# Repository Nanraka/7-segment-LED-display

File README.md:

# 7 segment LED display

## What is it?
Seven-segment LEDs are commonly used to display numbers, but by combining multiple units, it is also possible to display images and arbitrary patterns.  
I built a system that controls a large number of seven-segment LEDs to display image data and custom-designed patterns as a large-scale display.

For more details, see: > https://elchika.com/article/256d17d7-ee96-4fee-8e8a-b19cc3068b17/

---
## HW

SPRESENSE was used for control.  
The seven-segment LEDs were controlled using a shift register with a dynamic (multiplexed) driving method.

The PCB design data is available here: > https://github.com/Nanraka/7-segment-LED-display/tree/main/schematics

Please refer to the table below for the connections to the display.  
To distribute the signal lines, I built a custom Arduino shield mounted on the SPRESENSE.

| Spresense Extension Board Pin | Display Pin | Description |
|-----------------------------|------------------------|------|
| D13 (SCK)                   | SCLK                   | SPI clock signal |
| D11 (MOSI)                  | SER, TSER              | Data input (branched to SER and TSER) |
| D9 (CS)                     | CS                     | Chip select (Anode-side shift register) |
| D9                          | RESET                  | Shift register output enable |
| D3                          | TRCLK                  | Chip select (Cathode-side shift register) |
| D1                          | OE                     | Shift register output enable |
| GND                         | GND                    | Ground (common reference) |

⚠️ Please connect a dedicated power supply to the VCC terminal of the seven-segment display.  
⚠️ Do not connect it to the SPRESENSE Vout 5V pin.

---
## SW

The data sent from SPRESENSE to the display is prepared in advance on a PC.  
Python is used to convert the image data to be displayed into binary data.

The software data is available here: > https://github.com/Nanraka/7-segment-LED-display/tree/main/src

### 1. `make_base_csv.py`
This script generates mask data.

### 2. `img_2_serial.py`
This script performs the following processes:

- Resizes the input image  
- Converts the image to a binary (black-and-white) format, reads it column by column, converts it into serial data, and saves the result as `.txt` and `.csv` files  
- Rearranges the serial data into an order that can be visually recognized as an image by humans, and saves it as a `.csv` file

### 3. `make_data_for_7seg.py`
This script performs the following processes:

- Loads mask data that defines the positions of the seven-segment digits  
- Combines the image serial data with the mask data to generate data for displaying on the seven-segment LEDs

### 4. `7seg_spresense.ino`
- This program sends data to the seven-segment display in LSB-first order.
- The `.txt` file generated by `make_data_for_7seg.py` is stored on a microSD card and read by the SPRESENSE for use.

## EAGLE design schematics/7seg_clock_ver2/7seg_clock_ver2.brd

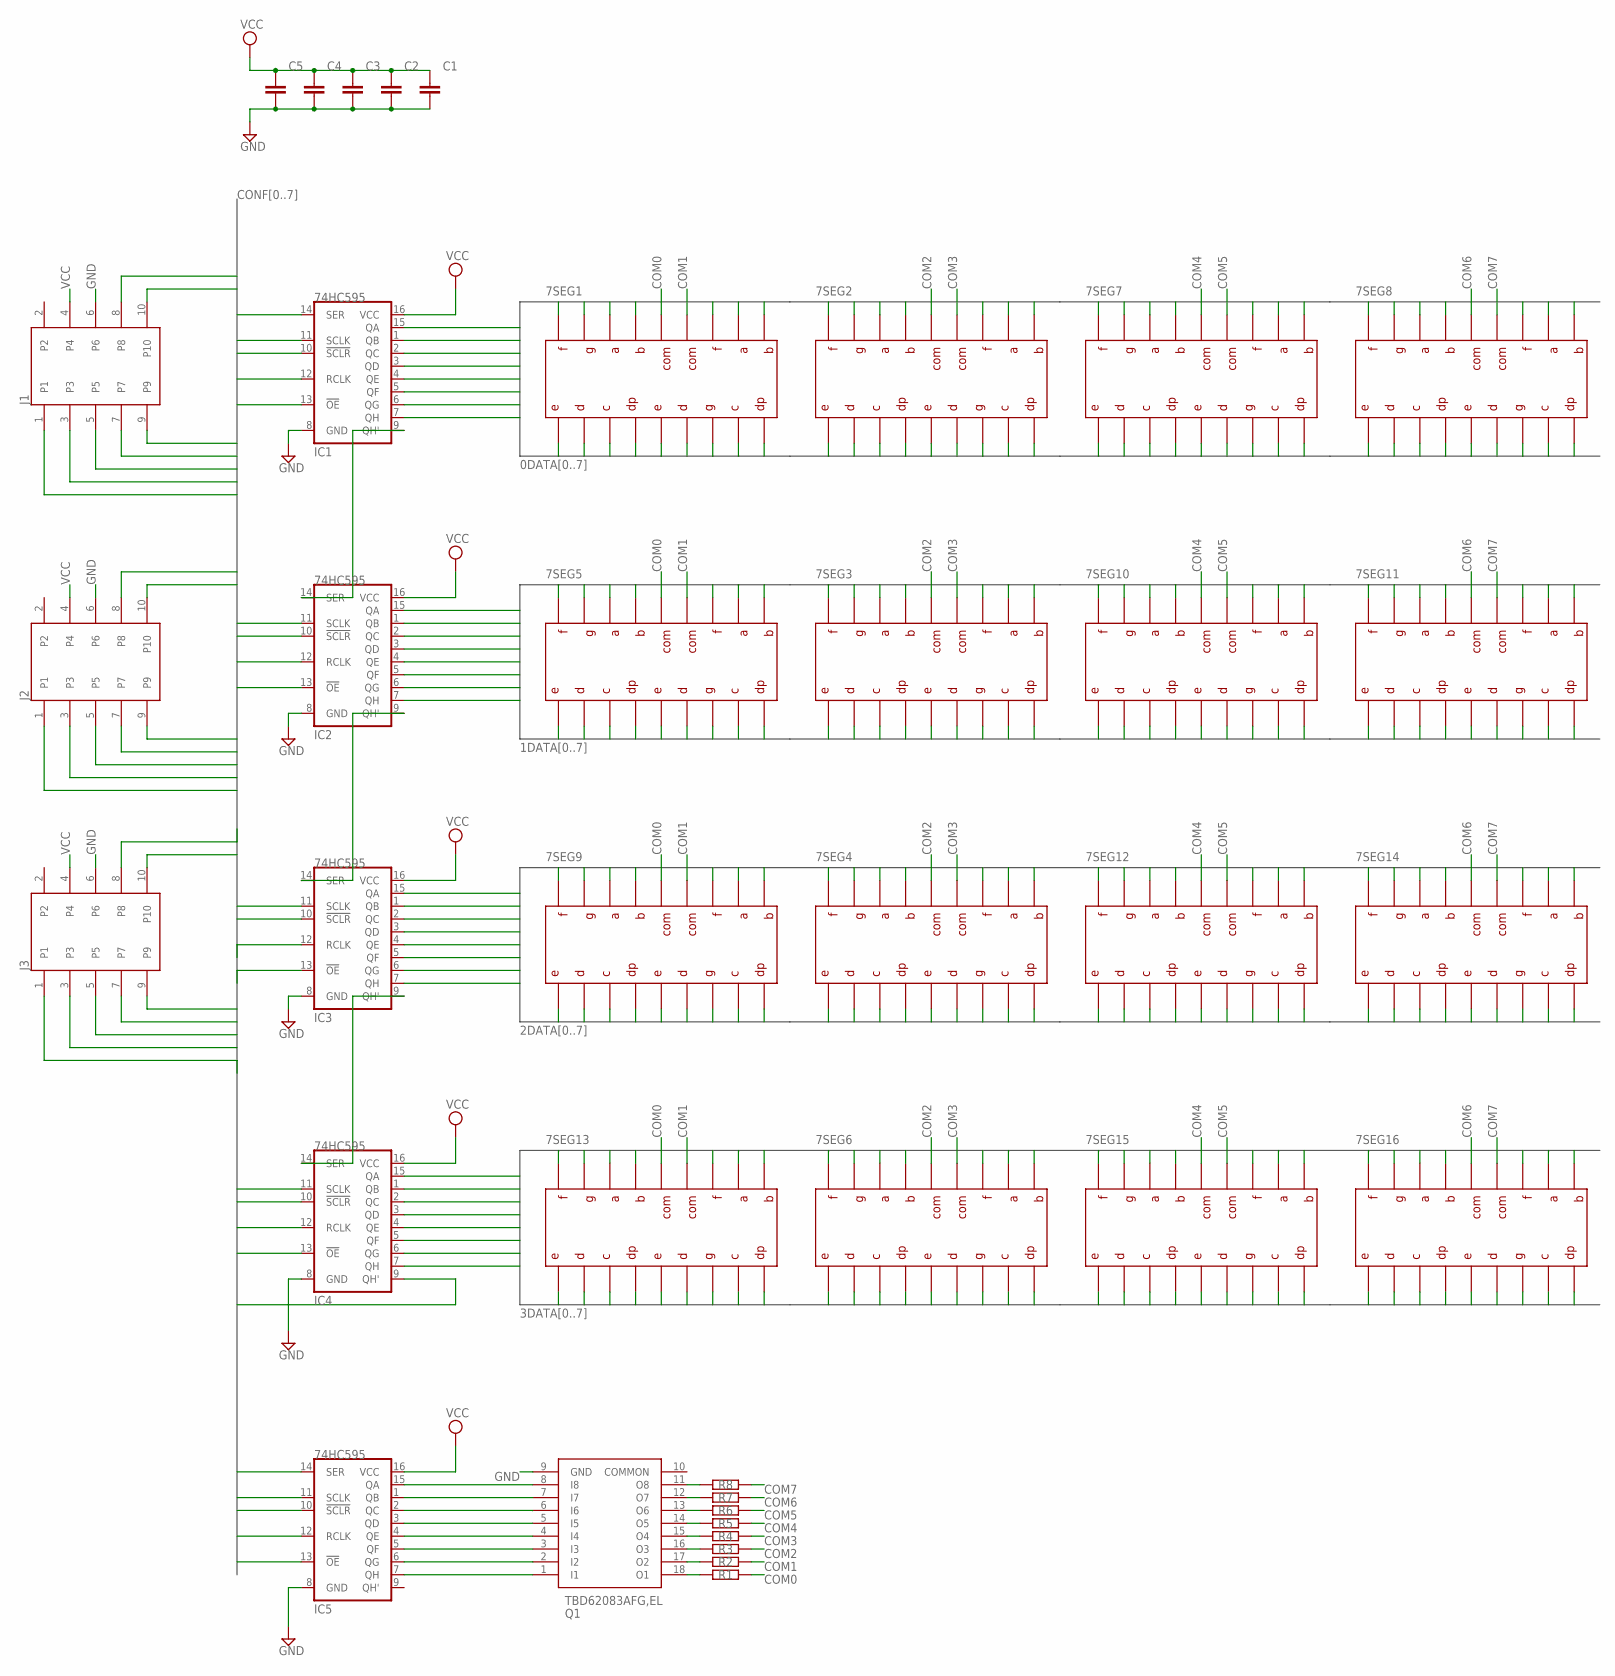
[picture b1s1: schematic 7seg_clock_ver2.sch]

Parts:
7SEG1, 7SEG2, 7SEG3, 7SEG4, 7SEG5, 7SEG6, 7SEG7, 7SEG8, 7SEG9, 7SEG10, 7SEG11, 7SEG12, 7SEG13, 7SEG14, 7SEG15, 7SEG16: SL-3264
C1, C2, C3, C4, C5: C_CHIP-0603(1608-METRIC); CAPC1608X85
IC1, IC2, IC3, IC4, IC5: 74HC595; SO16
J1, J2, J3: 1241050-5; TE_1241050-5
Q1: TBD62083AFG,EL; SOIC127P1030X245-18N
R1, R2, R3, R4, R5, R6, R7, R8: R_CHIP-0603(1608-METRIC); RESC1608X60

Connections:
0DATA0: 7SEG1.P$10, 7SEG1.P$15, 7SEG2.P$10, 7SEG2.P$15, 7SEG7.P$10, 7SEG7.P$15, 7SEG8.P$10, 7SEG8.P$15, IC1.15 (QA)
0DATA1: 7SEG1.P$12, 7SEG1.P$18, 7SEG2.P$12, 7SEG2.P$18, 7SEG7.P$12, 7SEG7.P$18, 7SEG8.P$12, 7SEG8.P$18, IC1.1 (QB)
0DATA2: 7SEG1.P$7, 7SEG1.P$17, 7SEG2.P$7, 7SEG2.P$17, 7SEG7.P$7, 7SEG7.P$17, 7SEG8.P$7, 7SEG8.P$17, IC1.2 (QC)
0DATA3: 7SEG1.P$11, 7SEG1.P$16, 7SEG2.P$11, 7SEG2.P$16, 7SEG7.P$11, 7SEG7.P$16, 7SEG8.P$11, 7SEG8.P$16, IC1.3 (QD)
0DATA4: 7SEG1.P$4, 7SEG1.P$9, 7SEG2.P$4, 7SEG2.P$9, 7SEG7.P$4, 7SEG7.P$9, 7SEG8.P$4, 7SEG8.P$9, IC1.4 (QE)
0DATA5: 7SEG1.P$3, 7SEG1.P$8, 7SEG2.P$3, 7SEG2.P$8, 7SEG7.P$3, 7SEG7.P$8, 7SEG8.P$3, 7SEG8.P$8, IC1.5 (QF)
0DATA6: 7SEG1.P$2, 7SEG1.P$6, 7SEG2.P$2, 7SEG2.P$6, 7SEG7.P$2, 7SEG7.P$6, 7SEG8.P$2, 7SEG8.P$6, IC1.6 (QG)
0DATA7: 7SEG1.P$1, 7SEG1.P$5, 7SEG2.P$1, 7SEG2.P$5, 7SEG7.P$1, 7SEG7.P$5, 7SEG8.P$1, 7SEG8.P$5, IC1.7 (QH)
1DATA0: 7SEG3.P$10, 7SEG3.P$15, 7SEG5.P$10, 7SEG5.P$15, 7SEG10.P$10, 7SEG10.P$15, 7SEG11.P$10, 7SEG11.P$15, IC2.15 (QA)
1DATA1: 7SEG3.P$12, 7SEG3.P$18, 7SEG5.P$12, 7SEG5.P$18, 7SEG10.P$12, 7SEG10.P$18, 7SEG11.P$12, 7SEG11.P$18, IC2.1 (QB)
1DATA2: 7SEG3.P$7, 7SEG3.P$17, 7SEG5.P$7, 7SEG5.P$17, 7SEG10.P$7, 7SEG10.P$17, 7SEG11.P$7, 7SEG11.P$17, IC2.2 (QC)
1DATA3: 7SEG3.P$11, 7SEG3.P$16, 7SEG5.P$11, 7SEG5.P$16, 7SEG10.P$11, 7SEG10.P$16, 7SEG11.P$11, 7SEG11.P$16, IC2.3 (QD)
1DATA4: 7SEG3.P$4, 7SEG3.P$9, 7SEG5.P$4, 7SEG5.P$9, 7SEG10.P$4, 7SEG10.P$9, 7SEG11.P$4, 7SEG11.P$9, IC2.4 (QE)
1DATA5: 7SEG3.P$3, 7SEG3.P$8, 7SEG5.P$3, 7SEG5.P$8, 7SEG10.P$3, 7SEG10.P$8, 7SEG11.P$3, 7SEG11.P$8, IC2.5 (QF)
1DATA6: 7SEG3.P$2, 7SEG3.P$6, 7SEG5.P$2, 7SEG5.P$6, 7SEG10.P$2, 7SEG10.P$6, 7SEG11.P$2, 7SEG11.P$6, IC2.6 (QG)
1DATA7: 7SEG3.P$1, 7SEG3.P$5, 7SEG5.P$1, 7SEG5.P$5, 7SEG10.P$1, 7SEG10.P$5, 7SEG11.P$1, 7SEG11.P$5, IC2.7 (QH)
2DATA0: 7SEG4.P$10, 7SEG4.P$15, 7SEG9.P$10, 7SEG9.P$15, 7SEG12.P$10, 7SEG12.P$15, 7SEG14.P$10, 7SEG14.P$15, IC3.15 (QA)
2DATA1: 7SEG4.P$12, 7SEG4.P$18, 7SEG9.P$12, 7SEG9.P$18, 7SEG12.P$12, 7SEG12.P$18, 7SEG14.P$12, 7SEG14.P$18, IC3.1 (QB)
2DATA2: 7SEG4.P$7, 7SEG4.P$17, 7SEG9.P$7, 7SEG9.P$17, 7SEG12.P$7, 7SEG12.P$17, 7SEG14.P$7, 7SEG14.P$17, IC3.2 (QC)
2DATA3: 7SEG4.P$11, 7SEG4.P$16, 7SEG9.P$11, 7SEG9.P$16, 7SEG12.P$11, 7SEG12.P$16, 7SEG14.P$11, 7SEG14.P$16, IC3.3 (QD)
2DATA4: 7SEG4.P$4, 7SEG4.P$9, 7SEG9.P$4, 7SEG9.P$9, 7SEG12.P$4, 7SEG12.P$9, 7SEG14.P$4, 7SEG14.P$9, IC3.4 (QE)
2DATA5: 7SEG4.P$3, 7SEG4.P$8, 7SEG9.P$3, 7SEG9.P$8, 7SEG12.P$3, 7SEG12.P$8, 7SEG14.P$3, 7SEG14.P$8, IC3.5 (QF)
2DATA6: 7SEG4.P$2, 7SEG4.P$6, 7SEG9.P$2, 7SEG9.P$6, 7SEG12.P$2, 7SEG12.P$6, 7SEG14.P$2, 7SEG14.P$6, IC3.6 (QG)
2DATA7: 7SEG4.P$1, 7SEG4.P$5, 7SEG9.P$1, 7SEG9.P$5, 7SEG12.P$1, 7SEG12.P$5, 7SEG14.P$1, 7SEG14.P$5, IC3.7 (QH)
3DATA0: 7SEG6.P$10, 7SEG6.P$15, 7SEG13.P$10, 7SEG13.P$15, 7SEG15.P$10, 7SEG15.P$15, 7SEG16.P$10, 7SEG16.P$15, IC4.15 (QA)
3DATA1: 7SEG6.P$12, 7SEG6.P$18, 7SEG13.P$12, 7SEG13.P$18, 7SEG15.P$12, 7SEG15.P$18, 7SEG16.P$12, 7SEG16.P$18, IC4.1 (QB)
3DATA2: 7SEG6.P$7, 7SEG6.P$17, 7SEG13.P$7, 7SEG13.P$17, 7SEG15.P$7, 7SEG15.P$17, 7SEG16.P$7, 7SEG16.P$17, IC4.2 (QC)
3DATA3: 7SEG6.P$11, 7SEG6.P$16, 7SEG13.P$11, 7SEG13.P$16, 7SEG15.P$11, 7SEG15.P$16, 7SEG16.P$11, 7SEG16.P$16, IC4.3 (QD)
3DATA4: 7SEG6.P$4, 7SEG6.P$9, 7SEG13.P$4, 7SEG13.P$9, 7SEG15.P$4, 7SEG15.P$9, 7SEG16.P$4, 7SEG16.P$9, IC4.4 (QE)
3DATA5: 7SEG6.P$3, 7SEG6.P$8, 7SEG13.P$3, 7SEG13.P$8, 7SEG15.P$3, 7SEG15.P$8, 7SEG16.P$3, 7SEG16.P$8, IC4.5 (QF)
3DATA6: 7SEG6.P$2, 7SEG6.P$6, 7SEG13.P$2, 7SEG13.P$6, 7SEG15.P$2, 7SEG15.P$6, 7SEG16.P$2, 7SEG16.P$6, IC4.6 (QG)
3DATA7: 7SEG6.P$1, 7SEG6.P$5, 7SEG13.P$1, 7SEG13.P$5, 7SEG15.P$1, 7SEG15.P$5, 7SEG16.P$1, 7SEG16.P$5, IC4.7 (QH)
COM0: 7SEG1.P$14, 7SEG5.P$14, 7SEG9.P$14, 7SEG13.P$14, R1.2
COM1: 7SEG1.P$13, 7SEG5.P$13, 7SEG9.P$13, 7SEG13.P$13, R2.2
COM2: 7SEG2.P$14, 7SEG3.P$14, 7SEG4.P$14, 7SEG6.P$14, R3.2
COM3: 7SEG2.P$13, 7SEG3.P$13, 7SEG4.P$13, 7SEG6.P$13, R4.2
COM4: 7SEG7.P$14, 7SEG10.P$14, 7SEG12.P$14, 7SEG15.P$14, R5.2
COM5: 7SEG7.P$13, 7SEG10.P$13, 7SEG12.P$13, 7SEG15.P$13, R6.2
COM6: 7SEG8.P$14, 7SEG11.P$14, 7SEG14.P$14, 7SEG16.P$14, R7.2
COM7: 7SEG8.P$13, 7SEG11.P$13, 7SEG14.P$13, 7SEG16.P$13, R8.2
CONF0: IC1.14 (SER), J1.1, J2.1, J3.1
CONF1: IC1.11 (SCLK), IC2.11 (SCLK), IC3.11 (SCLK), IC4.11 (SCLK), IC5.11 (SCLK), J1.7, J2.7, J3.7
CONF2: IC1.10 (!SCLR), IC2.10 (!SCLR), IC3.10 (!SCLR), IC4.10 (!SCLR), IC5.10 (!SCLR), J1.9, J2.9, J3.9
CONF3: IC1.12 (RCLK), IC2.12 (RCLK), IC3.12 (RCLK), IC4.12 (RCLK), IC5.12 (RCLK), J1.5, J2.5, J3.5
CONF4: IC1.13 (!OE), IC2.13 (!OE), IC3.13 (!OE), IC4.13 (!OE), IC5.13 (!OE), J1.3, J2.3, J3.3
CONF5: IC4.9 (QH'), J1.10, J2.10, J3.10
CONF6: IC5.14 (SER), J1.8, J2.8, J3.8
GND: C1.2, C2.2, C3.2, C4.2, C5.2, IC1.8 (GND), IC2.8 (GND), IC3.8 (GND), IC4.8 (GND), IC5.8 (GND), J1.6, J2.6, J3.6, Q1.9 (GND)
unnamed: IC1.9 (QH'), IC2.14 (SER)
unnamed: Q1.18 (O1), R1.1
unnamed: Q1.17 (O2), R2.1
unnamed: IC3.9 (QH'), IC4.14 (SER)
unnamed: Q1.16 (O3), R3.1
unnamed: IC5.7 (QH), Q1.1 (I1)
unnamed: IC5.6 (QG), Q1.2 (I2)
unnamed: IC5.5 (QF), Q1.3 (I3)
unnamed: IC5.4 (QE), Q1.4 (I4)
unnamed: Q1.15 (O4), R4.1
unnamed: Q1.14 (O5), R5.1
unnamed: IC5.3 (QD), Q1.5 (I5)
unnamed: IC5.2 (QC), Q1.6 (I6)
unnamed: IC5.1 (QB), Q1.7 (I7)
unnamed: IC5.15 (QA), Q1.8 (I8)
unnamed: Q1.13 (O6), R6.1
unnamed: Q1.12 (O7), R7.1
unnamed: Q1.11 (O8), R8.1
unnamed: IC2.9 (QH'), IC3.14 (SER)
VCC: C1.1, C2.1, C3.1, C4.1, C5.1, IC1.16 (VCC), IC2.16 (VCC), IC3.16 (VCC), IC4.16 (VCC), IC5.16 (VCC), J1.4, J2.4, J3.4

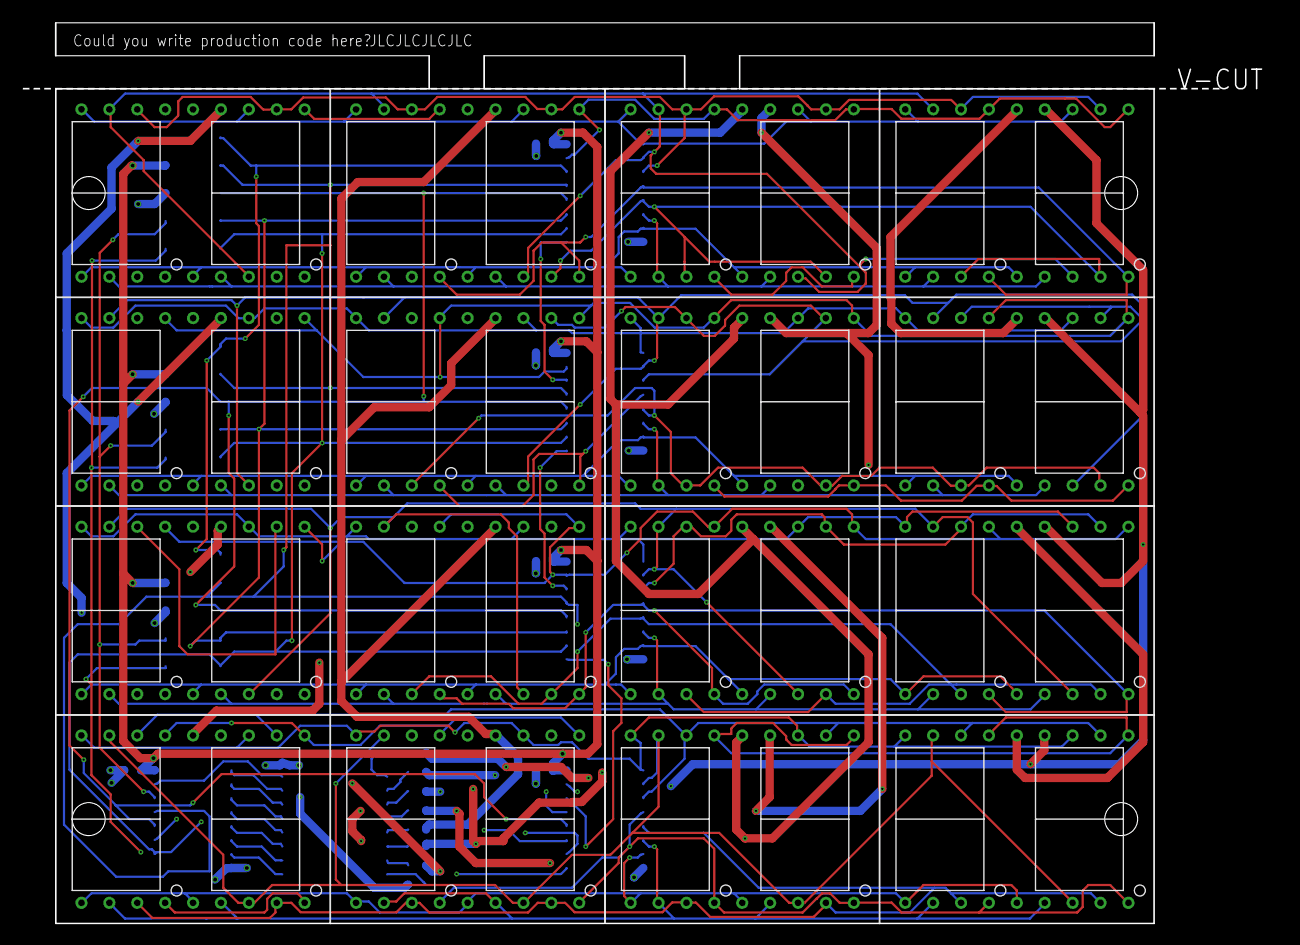
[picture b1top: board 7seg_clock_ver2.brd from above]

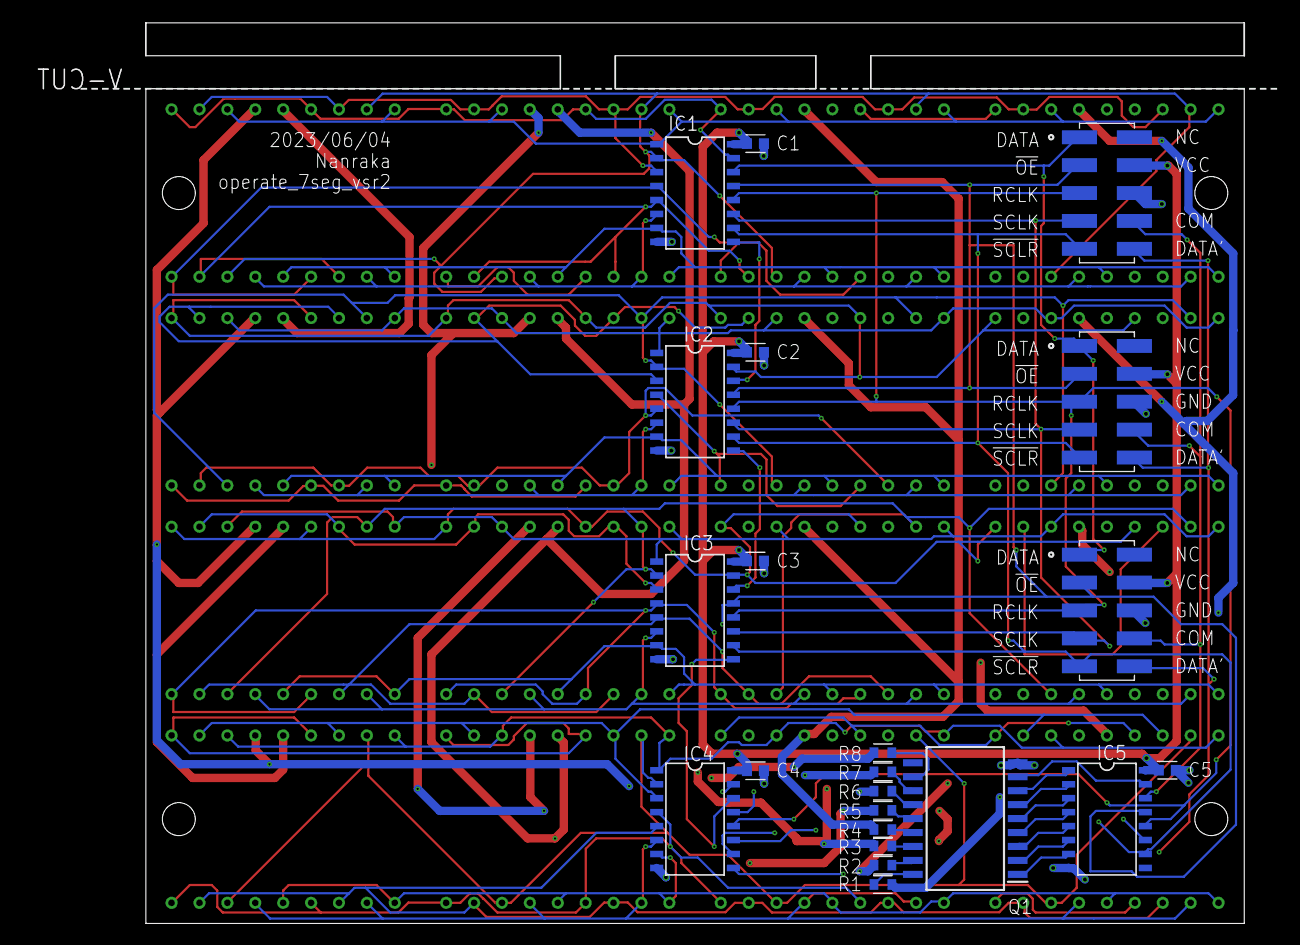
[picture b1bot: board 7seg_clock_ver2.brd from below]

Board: 4 copper layers, 114.2 x 81.9 mm, 38 parts (22 on the bottom side), 68 nets.

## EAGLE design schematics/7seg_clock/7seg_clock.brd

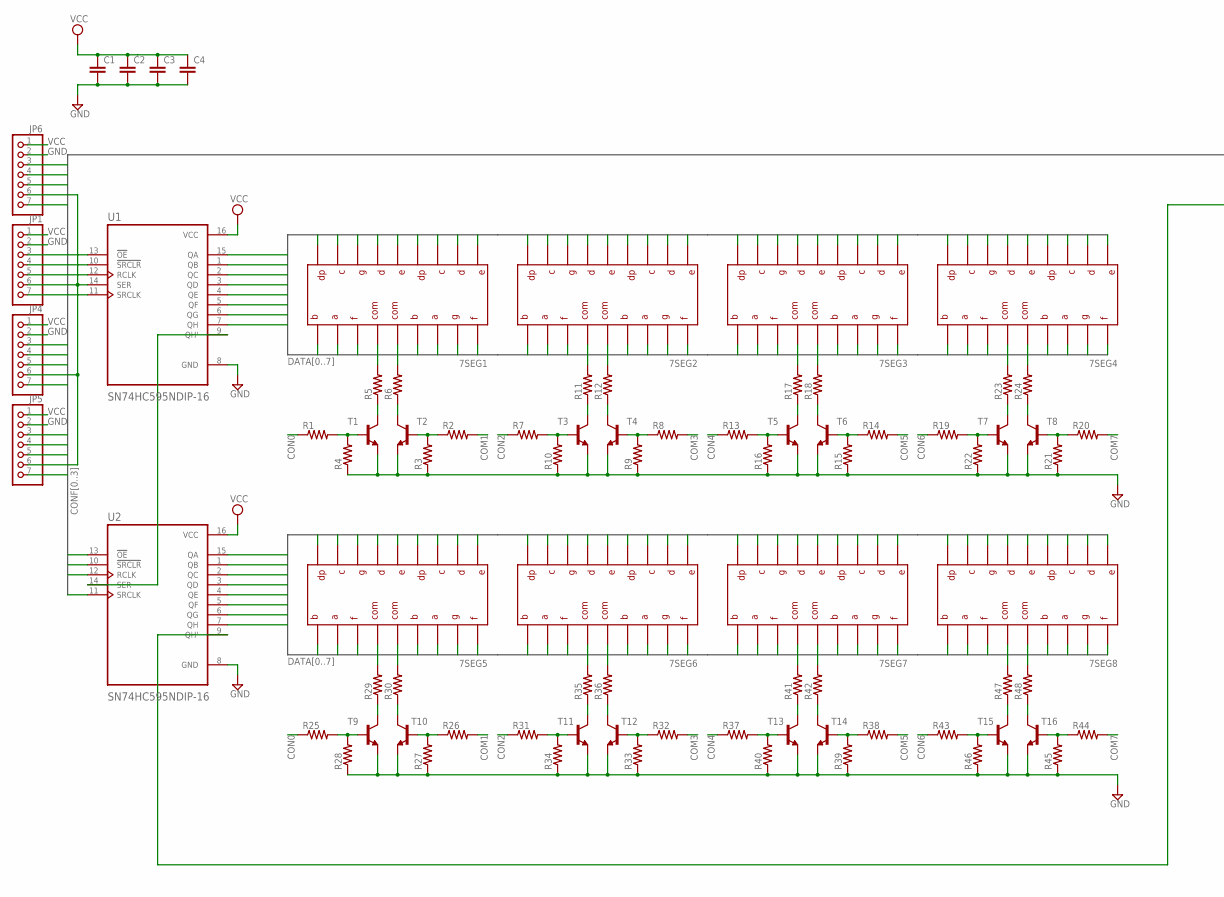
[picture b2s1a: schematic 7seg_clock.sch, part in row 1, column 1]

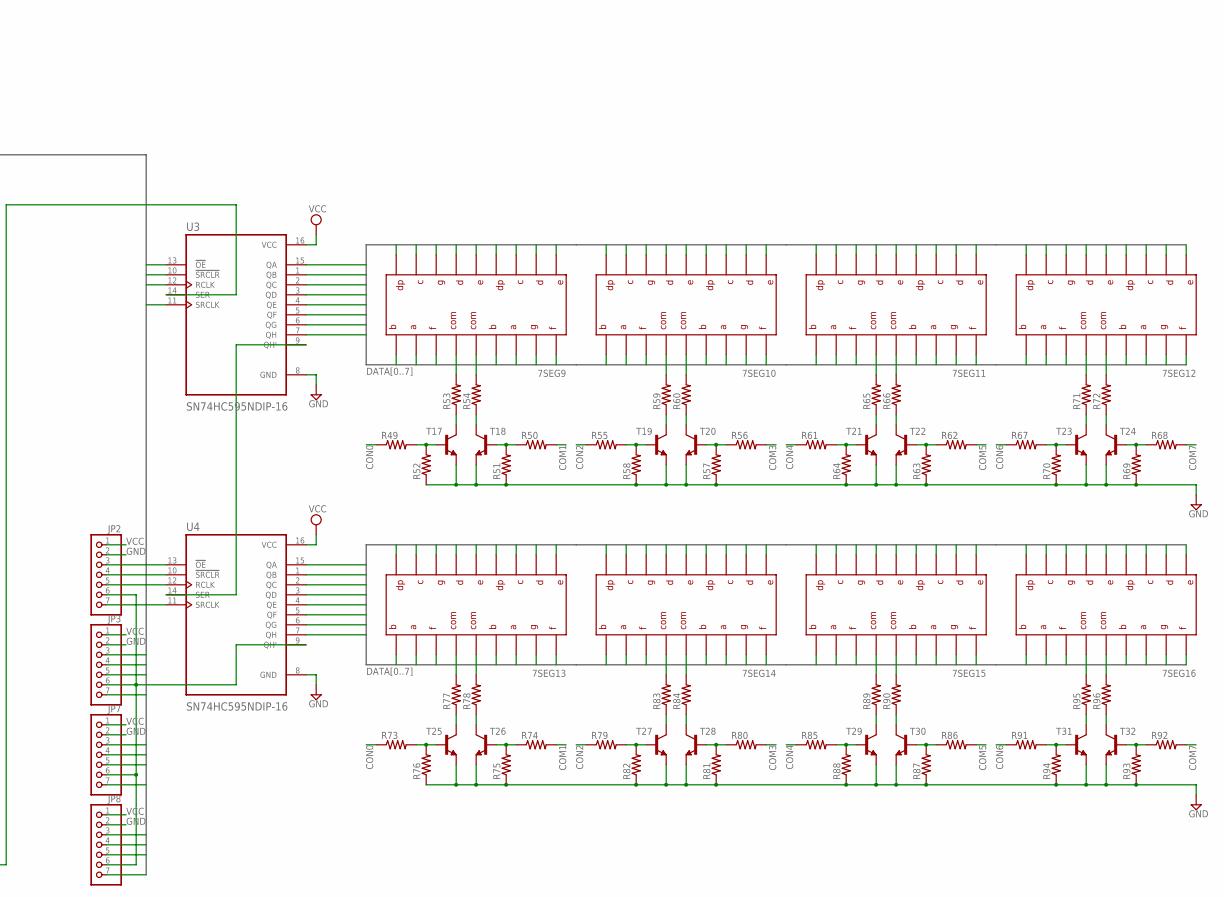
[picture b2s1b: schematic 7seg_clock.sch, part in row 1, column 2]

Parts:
7SEG1, 7SEG2, 7SEG3, 7SEG4, 7SEG5, 7SEG6, 7SEG7, 7SEG8, 7SEG9, 7SEG10, 7SEG11, 7SEG12, 7SEG13, 7SEG14, 7SEG15, 7SEG16: SL-3264
C1, C2, C3, C4: C-EU025-024X044; C025-024X044
JP1, JP2, JP3, JP4, JP5, JP6, JP7, JP8: PINHD-1X7; 1X07
R1, R2, R3, R4, R5, R6, R7, R8, R9, R10, R11, R12, R13, R14, R15, R16, R17, R18, R19, R20, R21, R22, R23, R24, R25, R26, R27, R28, R29, R30, R31, R32, R33, R34, R35, R36, R37, R38, R39, R40, R41, R42, R43, R44, R45, R46, R47, R48, R49, R50, R51, R52, R53, R54, R55, R56, R57, R58, R59, R60, R61, R62, R63, R64, R65, R66, R67, R68, R69, R70, R71, R72, R73, R74, R75, R76, R77, R78, R79, R80, R81, R82, R83, R84, R85, R86, R87, R88, R89, R90, R91, R92, R93, R94, R95, R96: R-US_0207/10; 0207/10
T1, T2, T3, T4, T5, T6, T7, T8, T9, T10, T11, T12, T13, T14, T15, T16, T17, T18, T19, T20, T21, T22, T23, T24, T25, T26, T27, T28, T29, T30, T31, T32: -NPN-TO92-BCE; TO92-BCE
U1, U2, U3, U4: SN74HC595NDIP-16; DIP794W45P254L1969H508Q16

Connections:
COM1: R2.2, R26.2, R50.2, R74.2
COM3: R8.2, R32.2, R56.2, R80.2
COM5: R14.2, R38.2, R62.2, R86.2
COM7: R20.2, R44.2, R68.2, R92.2
CON0: R1.1, R25.1, R49.1, R73.1
CON2: R7.1, R31.1, R55.1, R79.1
CON4: R13.1, R37.1, R61.1, R85.1
CON6: R19.1, R43.1, R67.1, R91.1
CONF0: JP1.3, JP2.3, JP3.3, JP4.3, JP5.3, JP6.3, JP7.3, JP8.3, U1.13 (!OE), U2.13 (!OE), U3.13 (!OE), U4.13 (!OE)
CONF1: JP1.4, JP2.4, JP3.4, JP4.4, JP5.4, JP6.4, JP7.4, JP8.4, U1.10 (!SRCLR), U2.10 (!SRCLR), U3.10 (!SRCLR), U4.10 (!SRCLR)
CONF2: JP1.5, JP2.5, JP3.5, JP4.5, JP5.5, JP6.5, JP7.5, JP8.5, U1.12 (RCLK), U2.12 (RCLK), U3.12 (RCLK), U4.12 (RCLK)
CONF3: JP1.7, JP2.7, JP3.7, JP4.7, JP5.7, JP6.7, JP7.7, JP8.7, U1.11 (SRCLK), U2.11 (SRCLK), U3.11 (SRCLK), U4.11 (SRCLK)
DATA0: 7SEG1.P$11, 7SEG1.P$16, 7SEG2.P$11, 7SEG2.P$16, 7SEG3.P$11, 7SEG3.P$16, 7SEG4.P$11, 7SEG4.P$16, 7SEG5.P$11, 7SEG5.P$16, 7SEG6.P$11, 7SEG6.P$16, 7SEG7.P$11, 7SEG7.P$16, 7SEG8.P$11, 7SEG8.P$16, 7SEG9.P$11, 7SEG9.P$16, 7SEG10.P$11, 7SEG10.P$16, 7SEG11.P$11, 7SEG11.P$16, 7SEG12.P$11, 7SEG12.P$16, 7SEG13.P$11, 7SEG13.P$16, 7SEG14.P$11, 7SEG14.P$16, 7SEG15.P$11, 7SEG15.P$16, 7SEG16.P$11, 7SEG16.P$16, U1.15 (QA), U2.15 (QA), U3.15 (QA), U4.15 (QA)
DATA1: 7SEG1.P$10, 7SEG1.P$15, 7SEG2.P$10, 7SEG2.P$15, 7SEG3.P$10, 7SEG3.P$15, 7SEG4.P$10, 7SEG4.P$15, 7SEG5.P$10, 7SEG5.P$15, 7SEG6.P$10, 7SEG6.P$15, 7SEG7.P$10, 7SEG7.P$15, 7SEG8.P$10, 7SEG8.P$15, 7SEG9.P$10, 7SEG9.P$15, 7SEG10.P$10, 7SEG10.P$15, 7SEG11.P$10, 7SEG11.P$15, 7SEG12.P$10, 7SEG12.P$15, 7SEG13.P$10, 7SEG13.P$15, 7SEG14.P$10, 7SEG14.P$15, 7SEG15.P$10, 7SEG15.P$15, 7SEG16.P$10, 7SEG16.P$15, U1.1 (QB), U2.1 (QB), U3.1 (QB), U4.1 (QB)
DATA2: 7SEG1.P$3, 7SEG1.P$8, 7SEG2.P$3, 7SEG2.P$8, 7SEG3.P$3, 7SEG3.P$8, 7SEG4.P$3, 7SEG4.P$8, 7SEG5.P$3, 7SEG5.P$8, 7SEG6.P$3, 7SEG6.P$8, 7SEG7.P$3, 7SEG7.P$8, 7SEG8.P$3, 7SEG8.P$8, 7SEG9.P$3, 7SEG9.P$8, 7SEG10.P$3, 7SEG10.P$8, 7SEG11.P$3, 7SEG11.P$8, 7SEG12.P$3, 7SEG12.P$8, 7SEG13.P$3, 7SEG13.P$8, 7SEG14.P$3, 7SEG14.P$8, 7SEG15.P$3, 7SEG15.P$8, 7SEG16.P$3, 7SEG16.P$8, U1.2 (QC), U2.2 (QC), U3.2 (QC), U4.2 (QC)
DATA3: 7SEG1.P$2, 7SEG1.P$6, 7SEG2.P$2, 7SEG2.P$6, 7SEG3.P$2, 7SEG3.P$6, 7SEG4.P$2, 7SEG4.P$6, 7SEG5.P$2, 7SEG5.P$6, 7SEG6.P$2, 7SEG6.P$6, 7SEG7.P$2, 7SEG7.P$6, 7SEG8.P$2, 7SEG8.P$6, 7SEG9.P$2, 7SEG9.P$6, 7SEG10.P$2, 7SEG10.P$6, 7SEG11.P$2, 7SEG11.P$6, 7SEG12.P$2, 7SEG12.P$6, 7SEG13.P$2, 7SEG13.P$6, 7SEG14.P$2, 7SEG14.P$6, 7SEG15.P$2, 7SEG15.P$6, 7SEG16.P$2, 7SEG16.P$6, U1.3 (QD), U2.3 (QD), U3.3 (QD), U4.3 (QD)
DATA4: 7SEG1.P$1, 7SEG1.P$5, 7SEG2.P$1, 7SEG2.P$5, 7SEG3.P$1, 7SEG3.P$5, 7SEG4.P$1, 7SEG4.P$5, 7SEG5.P$1, 7SEG5.P$5, 7SEG6.P$1, 7SEG6.P$5, 7SEG7.P$1, 7SEG7.P$5, 7SEG8.P$1, 7SEG8.P$5, 7SEG9.P$1, 7SEG9.P$5, 7SEG10.P$1, 7SEG10.P$5, 7SEG11.P$1, 7SEG11.P$5, 7SEG12.P$1, 7SEG12.P$5, 7SEG13.P$1, 7SEG13.P$5, 7SEG14.P$1, 7SEG14.P$5, 7SEG15.P$1, 7SEG15.P$5, 7SEG16.P$1, 7SEG16.P$5, U1.4 (QE), U2.4 (QE), U3.4 (QE), U4.4 (QE)
DATA5: 7SEG1.P$12, 7SEG1.P$18, 7SEG2.P$12, 7SEG2.P$18, 7SEG3.P$12, 7SEG3.P$18, 7SEG4.P$12, 7SEG4.P$18, 7SEG5.P$12, 7SEG5.P$18, 7SEG6.P$12, 7SEG6.P$18, 7SEG7.P$12, 7SEG7.P$18, 7SEG8.P$12, 7SEG8.P$18, 7SEG9.P$12, 7SEG9.P$18, 7SEG10.P$12, 7SEG10.P$18, 7SEG11.P$12, 7SEG11.P$18, 7SEG12.P$12, 7SEG12.P$18, 7SEG13.P$12, 7SEG13.P$18, 7SEG14.P$12, 7SEG14.P$18, 7SEG15.P$12, 7SEG15.P$18, 7SEG16.P$12, 7SEG16.P$18, U1.5 (QF), U2.5 (QF), U3.5 (QF), U4.5 (QF)
DATA6: 7SEG1.P$7, 7SEG1.P$17, 7SEG2.P$7, 7SEG2.P$17, 7SEG3.P$7, 7SEG3.P$17, 7SEG4.P$7, 7SEG4.P$17, 7SEG5.P$7, 7SEG5.P$17, 7SEG6.P$7, 7SEG6.P$17, 7SEG7.P$7, 7SEG7.P$17, 7SEG8.P$7, 7SEG8.P$17, 7SEG9.P$7, 7SEG9.P$17, 7SEG10.P$7, 7SEG10.P$17, 7SEG11.P$7, 7SEG11.P$17, 7SEG12.P$7, 7SEG12.P$17, 7SEG13.P$7, 7SEG13.P$17, 7SEG14.P$7, 7SEG14.P$17, 7SEG15.P$7, 7SEG15.P$17, 7SEG16.P$7, 7SEG16.P$17, U1.6 (QG), U2.6 (QG), U3.6 (QG), U4.6 (QG)
DATA7: 7SEG1.P$4, 7SEG1.P$9, 7SEG2.P$4, 7SEG2.P$9, 7SEG3.P$4, 7SEG3.P$9, 7SEG4.P$4, 7SEG4.P$9, 7SEG5.P$4, 7SEG5.P$9, 7SEG6.P$4, 7SEG6.P$9, 7SEG7.P$4, 7SEG7.P$9, 7SEG8.P$4, 7SEG8.P$9, 7SEG9.P$4, 7SEG9.P$9, 7SEG10.P$4, 7SEG10.P$9, 7SEG11.P$4, 7SEG11.P$9, 7SEG12.P$4, 7SEG12.P$9, 7SEG13.P$4, 7SEG13.P$9, 7SEG14.P$4, 7SEG14.P$9, 7SEG15.P$4, 7SEG15.P$9, 7SEG16.P$4, 7SEG16.P$9, U1.7 (QH), U2.7 (QH), U3.7 (QH), U4.7 (QH)
GND: C1.2, C2.2, C3.2, C4.2, JP1.2, JP2.2, JP3.2, JP4.2, JP5.2, JP6.2, JP7.2, JP8.2, R3.1, R4.1, R9.1, R10.1, R15.1, R16.1, R21.1, R22.1, R27.1, R28.1, R33.1, R34.1, R39.1, R40.1, R45.1, R46.1, R51.1, R52.1, R57.1, R58.1, R63.1, R64.1, R69.1, R70.1, R75.1, R76.1, R81.1, R82.1, R87.1, R88.1, R93.1, R94.1, T1.E, T2.E, T3.E, T4.E, T5.E, T6.E, T7.E, T8.E, T9.E, T10.E, T11.E, T12.E, T13.E, T14.E, T15.E, T16.E, T17.E, T18.E, T19.E, T20.E, T21.E, T22.E, T23.E, T24.E, T25.E, T26.E, T27.E, T28.E, T29.E, T30.E, T31.E, T32.E, U1.8 (GND), U2.8 (GND), U3.8 (GND), U4.8 (GND)
unnamed: R5.1, T1.C
unnamed: R6.1, T2.C
unnamed: R2.1, R3.2, T2.B
unnamed: R11.1, T3.C
unnamed: R12.1, T4.C
unnamed: R7.2, R10.2, T3.B
unnamed: R29.1, T9.C
unnamed: R8.1, R9.2, T4.B
unnamed: R1.2, R4.2, T1.B
unnamed: R17.1, T5.C
unnamed: R18.1, T6.C
unnamed: R30.1, T10.C
unnamed: R13.2, R16.2, T5.B
unnamed: R25.2, R28.2, T9.B
unnamed: R14.1, R15.2, T6.B
unnamed: R23.1, T7.C
unnamed: R24.1, T8.C
unnamed: R19.2, R22.2, T7.B
unnamed: R26.1, R27.2, T10.B
unnamed: R20.1, R21.2, T8.B
unnamed: R35.1, T11.C
unnamed: R36.1, T12.C
unnamed: R31.2, R34.2, T11.B
unnamed: R32.1, R33.2, T12.B
unnamed: R41.1, T13.C
unnamed: R42.1, T14.C
unnamed: R37.2, R40.2, T13.B
unnamed: R38.1, R39.2, T14.B
unnamed: R47.1, T15.C
unnamed: R48.1, T16.C
unnamed: R43.2, R46.2, T15.B
unnamed: R44.1, R45.2, T16.B
unnamed: JP1.6, JP4.6, JP5.6, JP6.6, U1.14 (SER)
unnamed: U1.9 (QH'), U2.14 (SER)
unnamed: U2.9 (QH'), U3.14 (SER)
unnamed: R53.1, T17.C
unnamed: R54.1, T18.C
unnamed: R49.2, R52.2, T17.B
unnamed: R50.1, R51.2, T18.B
unnamed: R59.1, T19.C
unnamed: R60.1, T20.C
unnamed: R55.2, R58.2, T19.B
unnamed: R56.1, R57.2, T20.B
unnamed: R65.1, T21.C
unnamed: R66.1, T22.C
unnamed: R61.2, R64.2, T21.B
unnamed: R62.1, R63.2, T22.B
unnamed: R71.1, T23.C
unnamed: R72.1, T24.C
unnamed: R67.2, R70.2, T23.B
unnamed: R68.1, R69.2, T24.B
unnamed: R77.1, T25.C
unnamed: R78.1, T26.C
unnamed: R73.2, R76.2, T25.B
unnamed: R74.1, R75.2, T26.B
unnamed: R83.1, T27.C
unnamed: R84.1, T28.C
unnamed: R79.2, R82.2, T27.B
unnamed: R80.1, R81.2, T28.B
unnamed: R89.1, T29.C
unnamed: R90.1, T30.C
unnamed: R85.2, R88.2, T29.B
unnamed: R86.1, R87.2, T30.B
unnamed: R95.1, T31.C
unnamed: R96.1, T32.C
unnamed: R91.2, R94.2, T31.B
unnamed: R92.1, R93.2, T32.B
unnamed: JP2.6, JP3.6, JP7.6, JP8.6, U4.9 (QH')
unnamed: U3.9 (QH'), U4.14 (SER)
P$13: 7SEG1.P$13, 7SEG2.P$13, 7SEG3.P$13, 7SEG4.P$13, 7SEG5.P$13, 7SEG6.P$13, 7SEG7.P$13, 7SEG8.P$13, 7SEG9.P$13, 7SEG10.P$13, 7SEG11.P$13, 7SEG12.P$13, 7SEG13.P$13, 7SEG14.P$13, 7SEG15.P$13, 7SEG16.P$13, R5.2, R11.2, R17.2, R23.2, R29.2, R35.2, R41.2, R47.2, R53.2, R59.2, R65.2, R71.2, R77.2, R83.2, R89.2, R95.2
P$14: 7SEG1.P$14, 7SEG2.P$14, 7SEG3.P$14, 7SEG4.P$14, 7SEG5.P$14, 7SEG6.P$14, 7SEG7.P$14, 7SEG8.P$14, 7SEG9.P$14, 7SEG10.P$14, 7SEG11.P$14, 7SEG12.P$14, 7SEG13.P$14, 7SEG14.P$14, 7SEG15.P$14, 7SEG16.P$14, R6.2, R12.2, R18.2, R24.2, R30.2, R36.2, R42.2, R48.2, R54.2, R60.2, R66.2, R72.2, R78.2, R84.2, R90.2, R96.2
VCC: C1.1, C2.1, JP1.1, JP2.1, JP3.1, JP4.1, JP5.1, JP6.1, JP7.1, JP8.1, U1.16 (VCC), U2.16 (VCC), U3.16 (VCC), U4.16 (VCC)
VCC1: C3.1, C4.1

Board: 2 copper layers, 160 parts (0 on the bottom side), 94 nets, no tracks yet.

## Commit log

2026-02-01 Add readme for 7 segment LED display
    Added detailed information about the 7 segment LED display project, including hardware and software components.
2026-02-01 Add MIT License to the project
2026-02-01 Removal of unnecessary files
2026-02-01 Fix formatting in README.md for SPRESENSE control
    Corrected formatting of the SPRESENSE control line.
2026-05-06 edit sch file name
2026-05-08 Modified the orientation to make the screen easier to see.
